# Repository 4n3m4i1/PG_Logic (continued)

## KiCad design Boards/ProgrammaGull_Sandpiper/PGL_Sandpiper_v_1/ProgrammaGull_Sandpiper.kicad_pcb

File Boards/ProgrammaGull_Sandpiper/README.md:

# ProgrammaGull Sandpiper
The Sandpiper is a complete educational development platform based on the Lattice UP5K.  
Designed for students in introductory FPGA labs and other interested parties.  
A plethora of user I/O options are integrated, allowing a complete system that can  
be used anywhere with minimal setup.

## Todo
v. Alpha
- Cleanup Layout
- Assess switching PSU
- Serialize Switch Inputs (Par -> Ser)
- Swap GPIO header to manufacturable part
- No ADC Version with 2x6 PMOD
- Add encoder, maybe bring back center DPAD button?
- Consolidate BOM (3x HCS595, discrete PNP and NPN driver for 7 seg)
  
## Errata
v. Alpha
- First board run has reversed UART TX/RX LED orientation (Fixed in KiCad files)
- First board run 7 segment common anode driver transistor bases leak through 74HCS596 input protection diode, all digits are always on. (Fixed in KiCad)

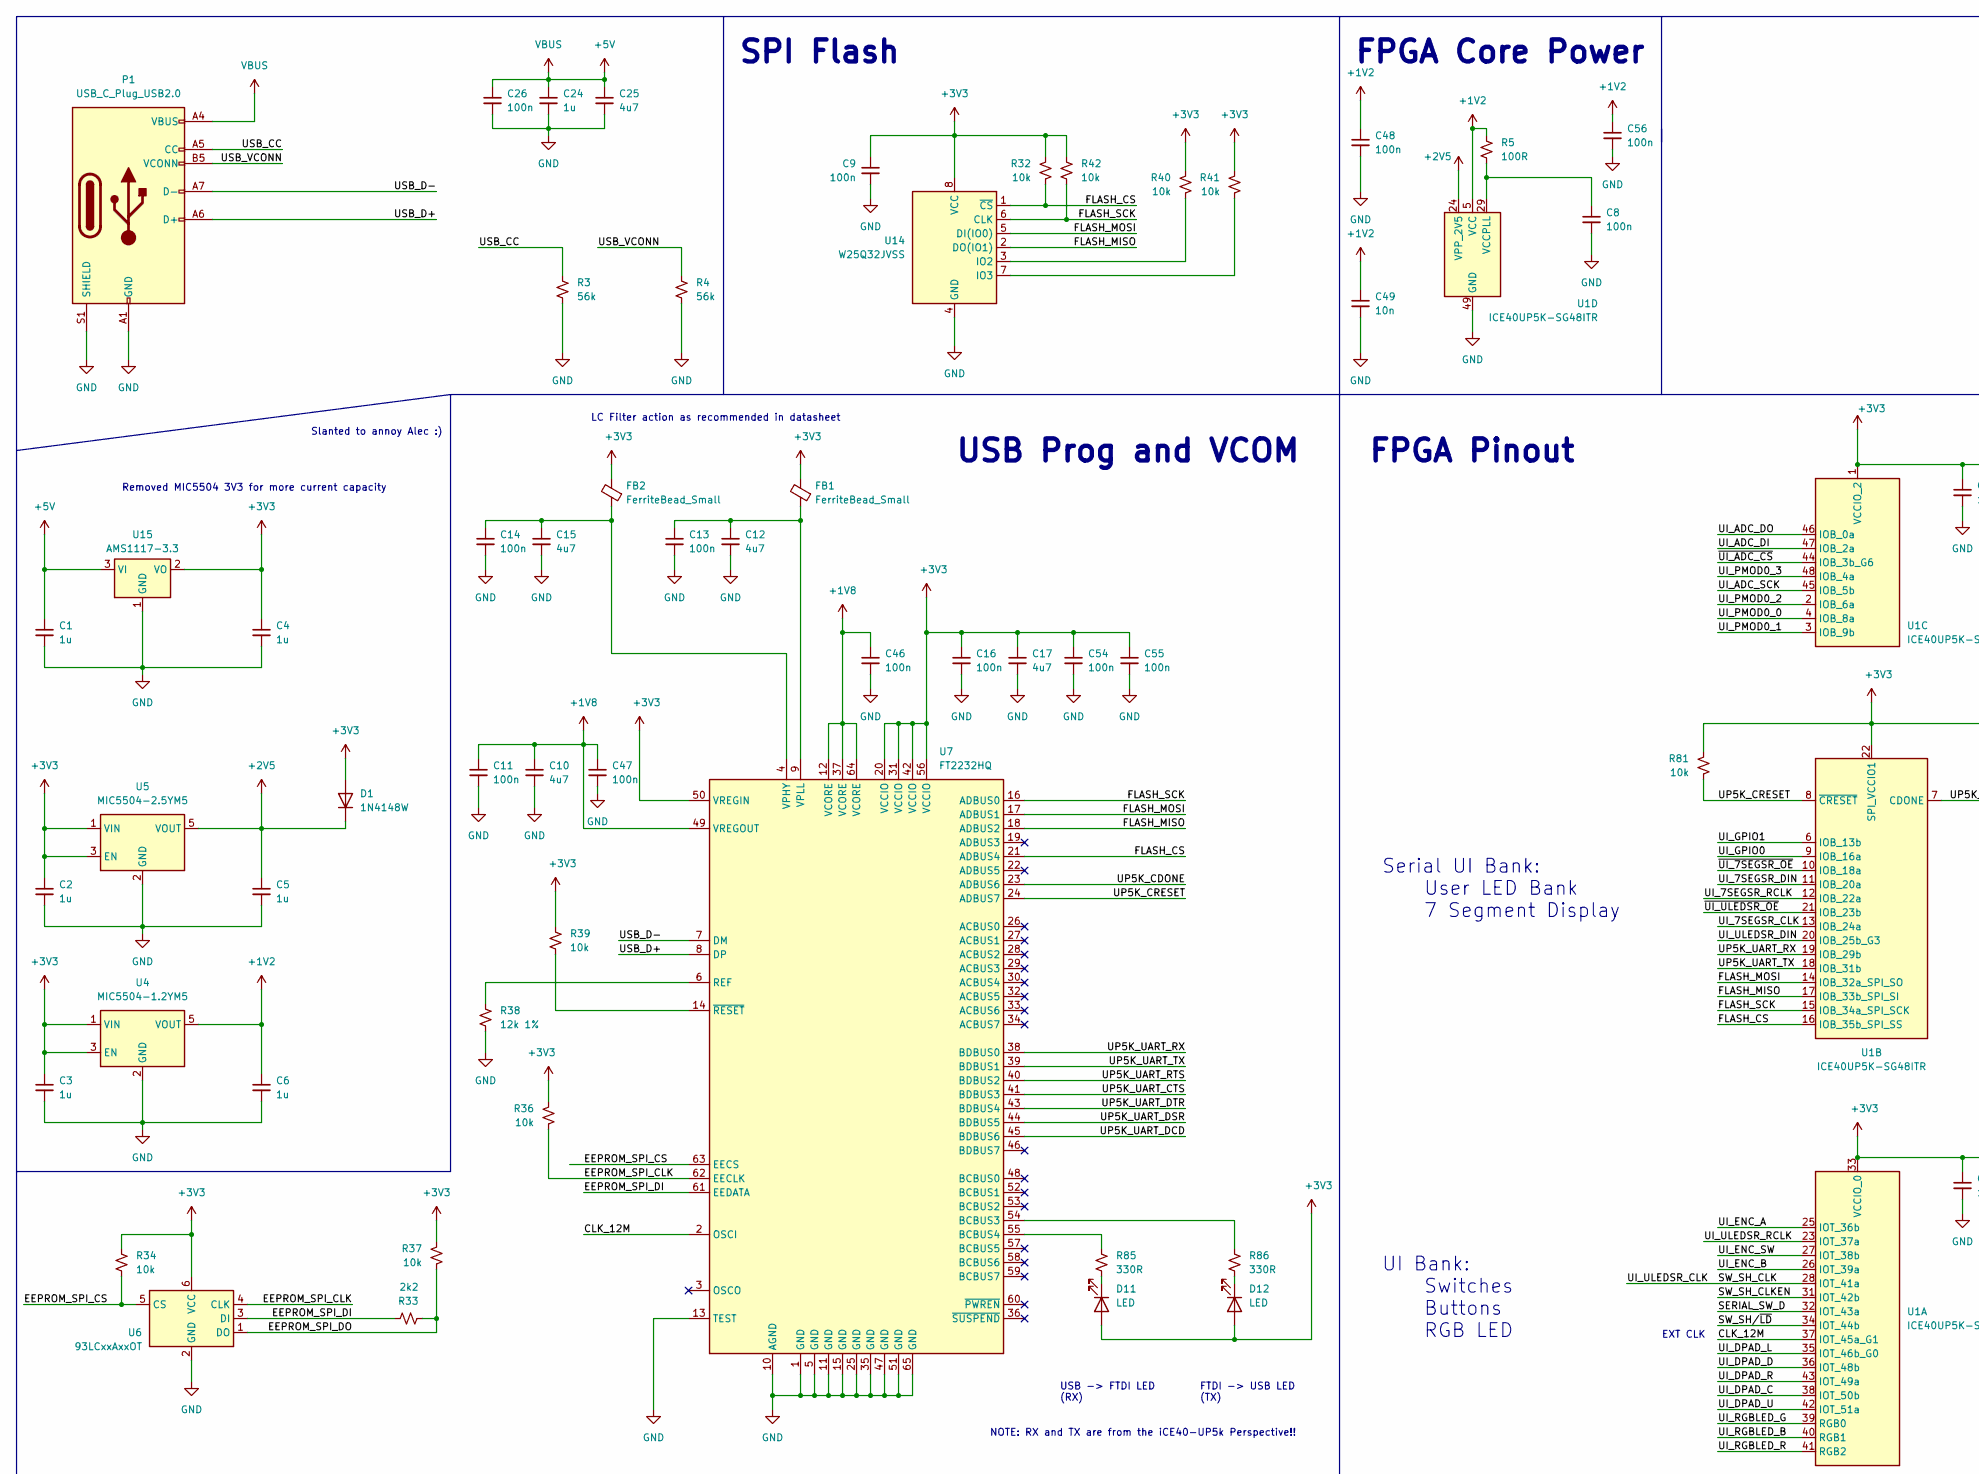
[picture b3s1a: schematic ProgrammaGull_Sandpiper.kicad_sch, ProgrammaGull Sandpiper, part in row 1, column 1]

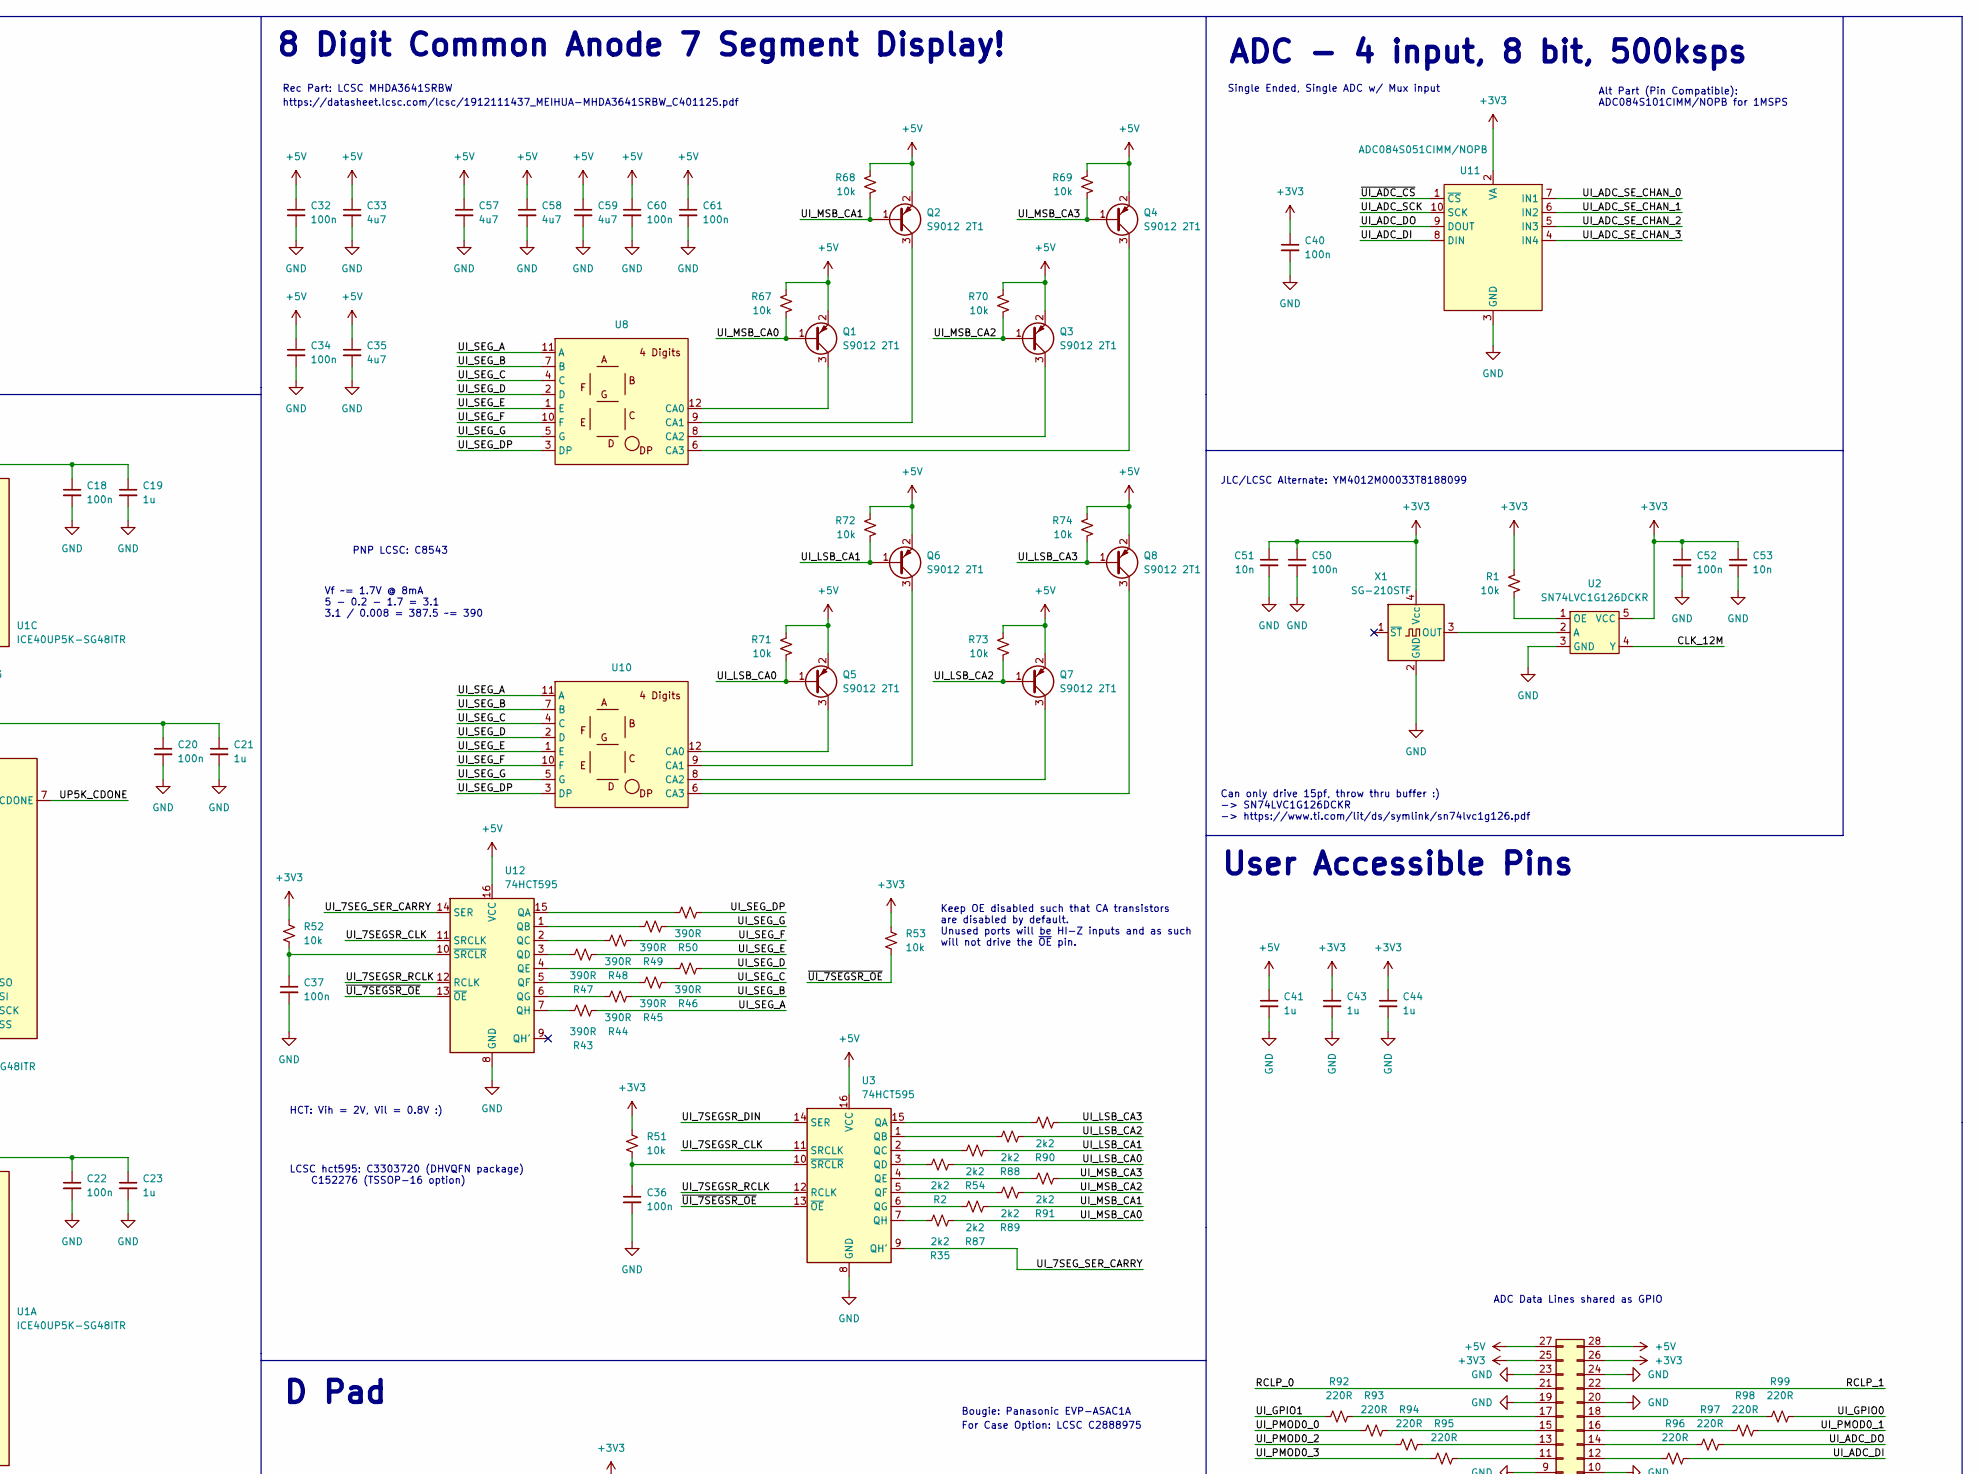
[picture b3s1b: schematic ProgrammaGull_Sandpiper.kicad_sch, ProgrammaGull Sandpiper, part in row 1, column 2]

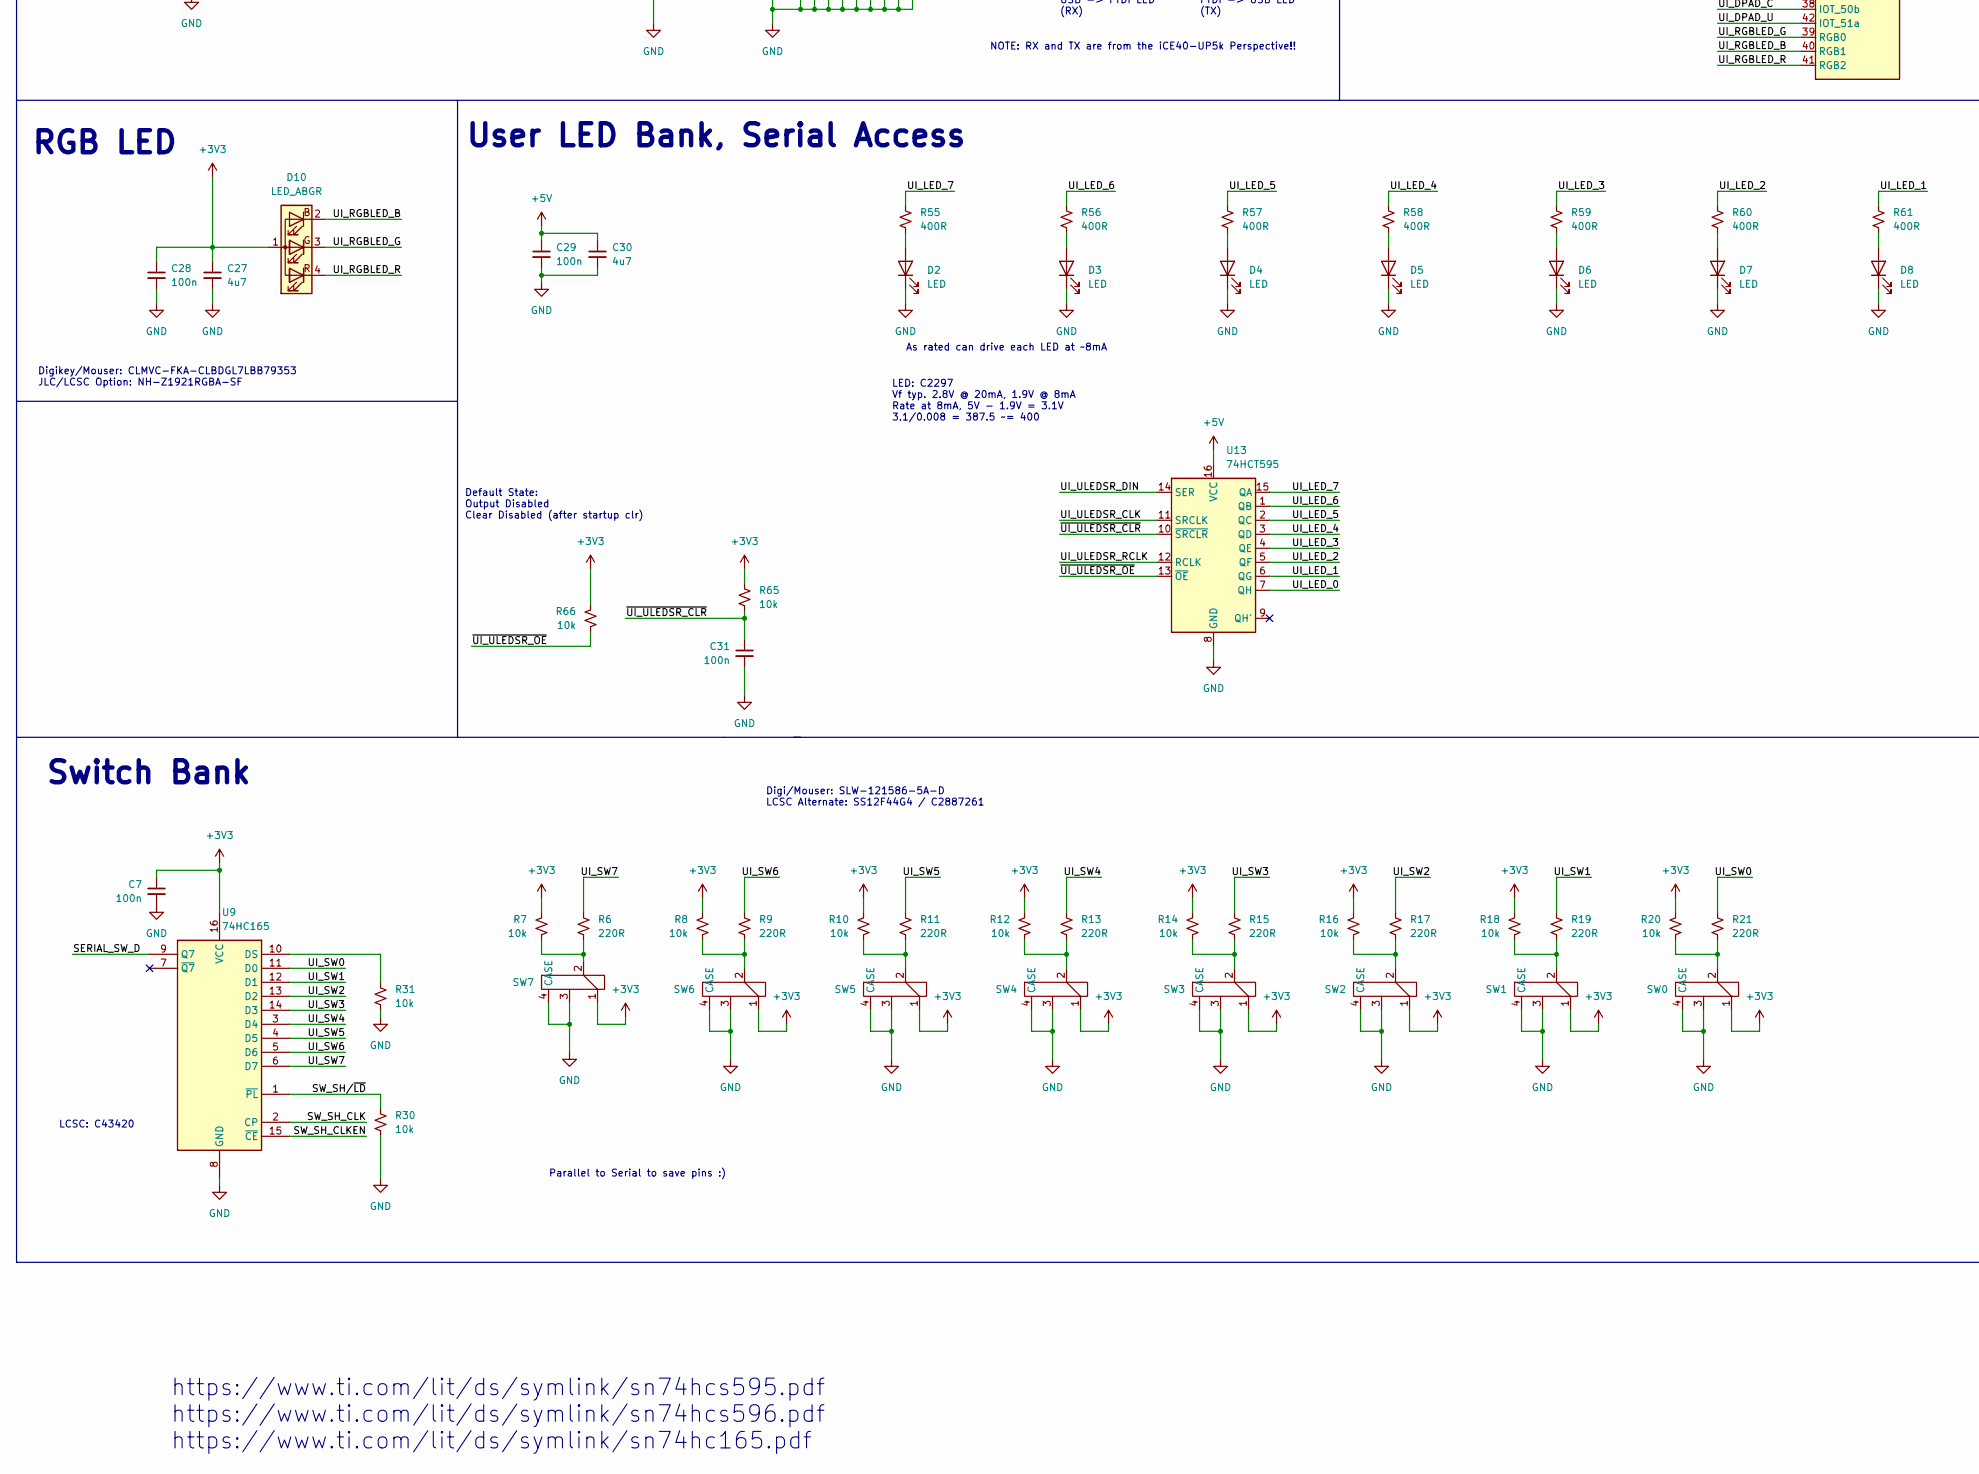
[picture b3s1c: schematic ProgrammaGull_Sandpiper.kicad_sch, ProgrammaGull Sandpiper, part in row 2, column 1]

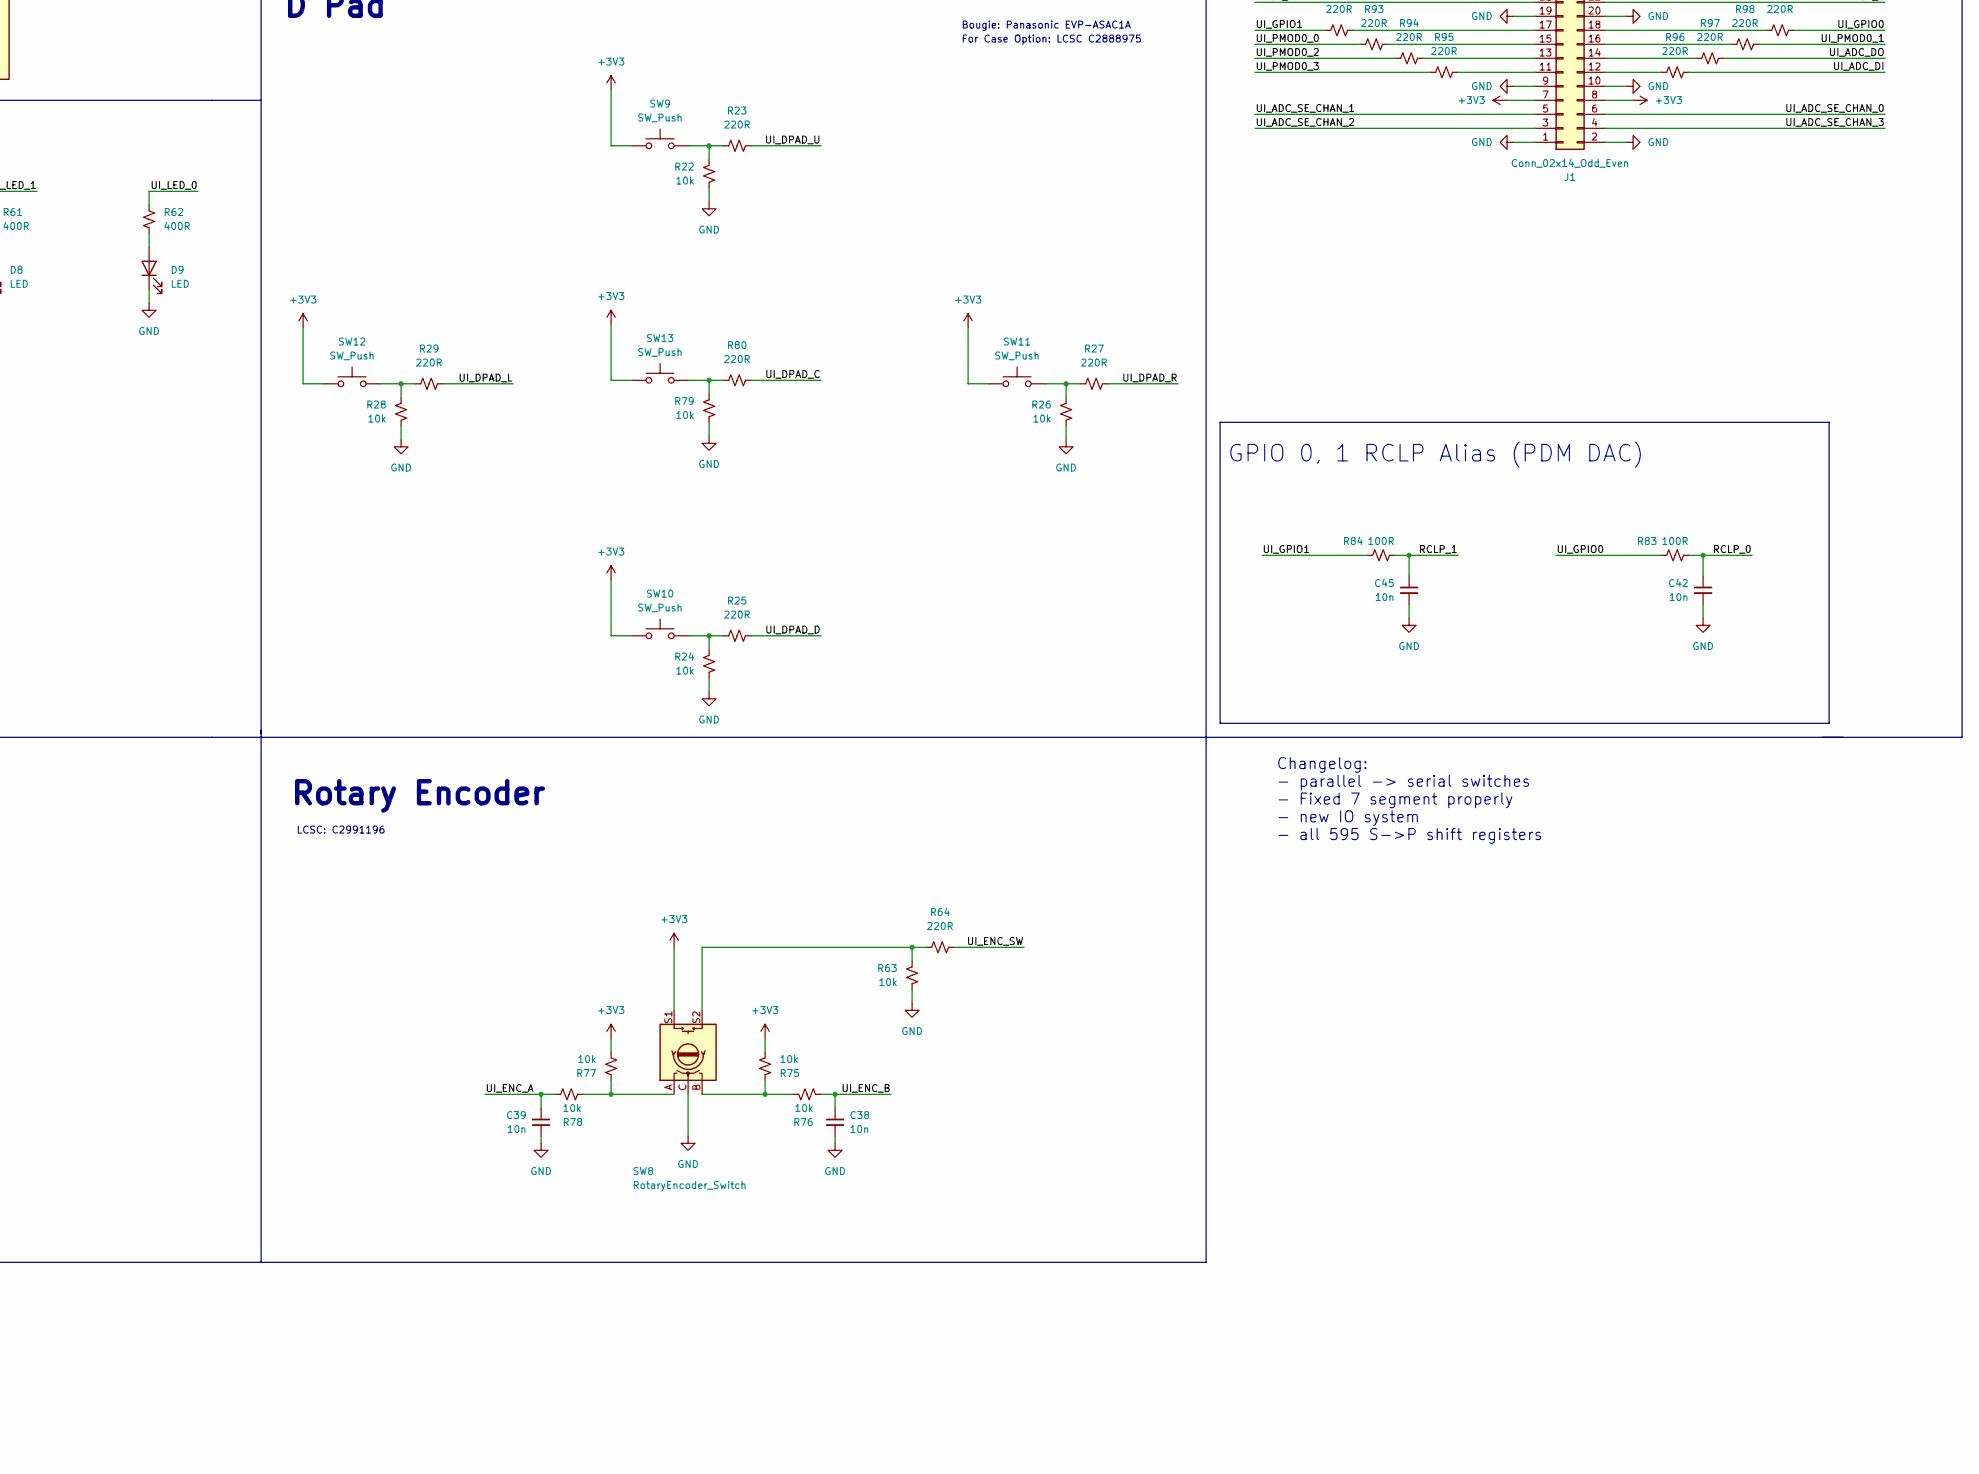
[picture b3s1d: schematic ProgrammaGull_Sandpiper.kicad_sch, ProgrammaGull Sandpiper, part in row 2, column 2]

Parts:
C1, C2, C3, C4, C5, C6, C19, C21, C23, C24, C41, C43, C44: 1u; C_0603_1608Metric
C7, C8, C9, C11, C13, C14, C16, C18, C20, C22, C26, C28, C29, C31, C32, C34, C36, C37, C40, C46, C47, C48, C50, C52, C54, C55, C56, C60, C61: 100n; C_0603_1608Metric
C10, C12, C15, C17, C25, C27, C30, C33, C35, C57, C58, C59: 4u7; C_0805_2012Metric
C38, C39, C42, C45, C49, C51, C53: 10n; C_0603_1608Metric
D1: 1N4148W; D_SOD-123
D2, D3, D4, D5, D6, D7, D8, D9, D11, D12: LED; LED_0805_2012Metric
D10: LED_ABGR; LED_Cree-PLCC4_2x2mm_CW
FB1, FB2: FerriteBead_Small; L_0603_1608Metric
J1: Conn_02x14_Odd_Even; PinSocket_2x14_P2.54mm_Horizontal
P1: USB_C_Plug_USB2.0; USB_C_Receptacle_GCT_USB4105-xx-A_16P_TopMnt_Horizontal
Q1, Q2, Q3, Q4, Q5, Q6, Q7, Q8: S9012 2T1; SOT-23
R1, R7, R8, R10, R12, R14, R16, R18, R20, R22, R24, R26, R28, R30, R31, R32, R34, R36, R37, R39, R40, R41, R42, R51, R52, R53, R63, R65, R66, R67, R68, R69, R70, R71, R72, R73, R74, R75, R76, R77, R78, R79, R81: 10k; R_0603_1608Metric
R2, R33, R35, R54, R87, R88, R89, R90, R91: 2k2; R_0603_1608Metric
R3, R4: 56k; R_0603_1608Metric
R5, R83, R84: 100R; R_0603_1608Metric
R6, R9, R11, R13, R15, R17, R19, R21: 220R; R_0603_1608Metric
R23, R25, R27, R29, R64, R80, R92, R93, R94, R95, R96, R97, R98, R99: 220R; R_0402_1005Metric
R38: 12k 1%; R_0603_1608Metric
R43, R44, R45, R46, R47, R48, R49, R50: 390R; R_0603_1608Metric
R55, R56, R57, R58, R59, R60, R61, R62: 400R; R_0603_1608Metric
R85, R86: 330R; R_0603_1608Metric
SW0, SW1, SW2, SW3, SW4, SW5, SW6, SW7: SLW-121586-5A-D
SW8: RotaryEncoder_Switch; RotaryEncoder_Alps_EC11E-Switch_Vertical_H20mm
SW9, SW10, SW11, SW12, SW13: SW_Push; TSC015A05518A
U1: ICE40UP5K-SG48ITR; QFN-48-1EP_7x7mm_P0.5mm_EP5.6x5.6mm
U2: SN74LVC1G126DCKR; SC70
U3, U12, U13: 74HCT595; DHVQFN-16-1EP_2.5x3.5mm_P0.5mm_EP1x2mm
U4: MIC5504-1.2YM5; SOT-23-5
U5: MIC5504-2.5YM5; SOT-23-5
U6: 93LCxxAxxOT; SOT-23-6
U7: FT2232HQ; QFN-64-1EP_9x9mm_P0.5mm_EP4.35x4.35mm
U8, U10: MHDA3641SRBW
U9: 74HC165; TSSOP-16_4.4x5mm_P0.65mm
U11: ADC084S051CIMM/NOPB; VSSOP-10_3x3mm_P0.5mm
U14: W25Q32JVSS; SOIC-8_5.23x5.23mm_P1.27mm
U15: AMS1117-3.3; SOT-223-3_TabPin2
X1: SG-210STF; Oscillator_SMD_SeikoEpson_SG210-4Pin_2.5x2.0mm

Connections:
+1V2: C6.1, C48.1, C49.1, C56.1, R5.2, U1.5 (VCC), U1.30 (VCC), U4.5 (VOUT)
+2V5: C5.1, D1.1 (K), U1.24 (VPP_2V5), U5.5 (VOUT)
+5V: C1.1, C24.1, C25.1, C26.1, C29.1, C30.1, C32.1, C33.1, C34.1, C35.1, C41.1, C57.1, C58.1, C59.1, C60.1, C61.1, J1.27, J1.28, P1.A4 (VBUS), P1.A9 (VBUS), P1.B4 (VBUS), P1.B9 (VBUS), Q1.2 (E), Q2.2 (E), Q3.2 (E), Q4.2 (E), Q5.2 (E), Q6.2 (E), Q7.2 (E), Q8.2 (E), R67.2, R68.2, R69.2, R70.2, R71.2, R72.2, R73.2, R74.2, U3.16 (VCC), U12.16 (VCC), U13.16 (VCC), U15.3 (VI)
/CLK_12M: U1.37 (IOT_45a_G1), U2.4 (Y), U7.2 (OSCI)
/EEPROM_SPI_CLK: R36.1, U6.4 (CLK), U7.62 (EECLK)
/EEPROM_SPI_CS: R34.1, U6.5 (CS), U7.63 (EECS)
/EEPROM_SPI_DI: R33.2, U6.3 (DI), U7.61 (EEDATA)
/EEPROM_SPI_DO: R33.1, R37.1, U6.1 (DO)
/FLASH_CS: R32.1, U1.16 (IOB_35b_SPI_SS), U7.21 (ADBUS4), U14.1 (~CS)
/FLASH_MISO: U1.17 (IOB_33b_SPI_SI), U7.18 (ADBUS2), U14.2 (DO(IO1))
/FLASH_MOSI: U1.14 (IOB_32a_SPI_SO), U7.17 (ADBUS1), U14.5 (DI(IO0))
/FLASH_SCK: R42.1, U1.15 (IOB_34a_SPI_SCK), U7.16 (ADBUS0), U14.6 (CLK)
/RCLP_0: C42.1, J1.21, R83.1
/RCLP_1: C45.1, J1.22, R84.1
/SERIAL_SW_D: U1.32 (IOT_43a), U9.9 (Q7)
/SW_SH_CLK: U1.28 (IOT_41a), U9.2 (CP), U13.11 (SRCLK)
/SW_SH_CLKEN: U1.31 (IOT_42b), U9.15 (~CE)
/SW_SH/~LD: R30.2, U1.34 (IOT_44b), U9.1 (~PL)
/UI_7SEGSR_CLK: U1.13 (IOB_24a), U3.11 (SRCLK), U12.11 (SRCLK)
/UI_7SEGSR_DIN: U1.11 (IOB_20a), U3.14 (SER)
/UI_7SEGSR_RCLK: U1.12 (IOB_22a), U3.12 (RCLK), U12.12 (RCLK)
/UI_7SEG_SER_CARRY: U3.9 (QH'), U12.14 (SER)
/UI_ADC_DI: R96.1, U1.47 (IOB_2a), U11.8 (DIN)
/UI_ADC_DO: R97.1, U1.46 (IOB_0a), U11.9 (DOUT)
/UI_ADC_SCK: U1.45 (IOB_5b), U11.10 (SCK)
/UI_ADC_SE_CHAN_0: J1.6, U11.7 (IN1)
/UI_ADC_SE_CHAN_1: J1.5, U11.6 (IN2)
/UI_ADC_SE_CHAN_2: J1.3, U11.5 (IN3)
/UI_ADC_SE_CHAN_3: J1.4, U11.4 (IN4)
/UI_DPAD_C: R80.1, U1.38 (IOT_50b)
/UI_DPAD_D: R25.1, U1.36 (IOT_48b)
/UI_DPAD_L: R29.1, U1.35 (IOT_46b_G0)
/UI_DPAD_R: R27.1, U1.43 (IOT_49a)
/UI_DPAD_U: R23.1, U1.42 (IOT_51a)
/UI_ENC_A: C39.1, R78.1, U1.25 (IOT_36b)
/UI_ENC_B: C38.1, R76.1, U1.26 (IOT_39a)
/UI_ENC_SW: R64.1, U1.27 (IOT_38b)
/UI_GPIO0: R83.2, R99.1, U1.9 (IOB_16a)
/UI_GPIO1: R84.2, R92.2, U1.6 (IOB_13b)
/UI_LED_0: R62.2, U13.7 (QH)
/UI_LED_1: R61.2, U13.6 (QG)
/UI_LED_2: R60.2, U13.5 (QF)
/UI_LED_3: R59.2, U13.4 (QE)
/UI_LED_4: R58.2, U13.3 (QD)
/UI_LED_5: R57.2, U13.2 (QC)
/UI_LED_6: R56.2, U13.1 (QB)
/UI_LED_7: R55.2, U13.15 (QA)
/UI_LSB_CA0: Q5.1 (B), R2.1, R71.1
/UI_LSB_CA1: Q6.1 (B), R54.1, R72.1
/UI_LSB_CA2: Q7.1 (B), R73.1, R88.1
/UI_LSB_CA3: Q8.1 (B), R74.1, R90.1
/UI_MSB_CA0: Q1.1 (B), R35.1, R67.1
/UI_MSB_CA1: Q2.1 (B), R68.1, R87.1
/UI_MSB_CA2: Q3.1 (B), R70.1, R89.1
/UI_MSB_CA3: Q4.1 (B), R69.1, R91.1
/UI_PMOD0_0: R93.2, U1.4 (IOB_8a)
/UI_PMOD0_1: R98.1, U1.3 (IOB_9b)
/UI_PMOD0_2: R94.2, U1.2 (IOB_6a)
/UI_PMOD0_3: R95.2, U1.48 (IOB_4a)
/UI_RGBLED_B: D10.2 (BK), U1.40 (RGB1)
/UI_RGBLED_G: D10.3 (GK), U1.39 (RGB0)
/UI_RGBLED_R: D10.4 (RK), U1.41 (RGB2)
/UI_SEG_A: R43.1, U8.11 (A), U10.11 (A)
/UI_SEG_B: R44.1, U8.7 (B), U10.7 (B)
/UI_SEG_C: R45.1, U8.4 (C), U10.4 (C)
/UI_SEG_D: R46.1, U8.2 (D), U10.2 (D)
/UI_SEG_DP: R50.1, U8.3 (DP), U10.3 (DP)
/UI_SEG_E: R47.1, U8.1 (E), U10.1 (E)
/UI_SEG_F: R48.1, U8.10 (F), U10.10 (F)
/UI_SEG_G: R49.1, U8.5 (G), U10.5 (G)
/UI_SW0: R21.2, U9.11 (D0)
/UI_SW1: R19.2, U9.12 (D1)
/UI_SW2: R17.2, U9.13 (D2)
/UI_SW3: R15.2, U9.14 (D3)
/UI_SW4: R13.2, U9.3 (D4)
/UI_SW5: R11.2, U9.4 (D5)
/UI_SW6: R9.2, U9.5 (D6)
/UI_SW7: R6.2, U9.6 (D7)
/UI_ULEDSR_DIN: U1.20 (IOB_25b_G3), U13.14 (SER)
/UI_ULEDSR_RCLK: U1.23 (IOT_37a), U13.12 (RCLK)
/UP5K_CDONE: U1.7 (CDONE), U7.23 (ADBUS6)
/UP5K_CRESET: R81.1, U1.8 (~CRESET), U7.24 (ADBUS7)
/UP5K_UART_CTS: U7.41 (BDBUS3)
/UP5K_UART_DCD: U7.45 (BDBUS6)
/UP5K_UART_DSR: U7.44 (BDBUS5)
/UP5K_UART_DTR: U7.43 (BDBUS4)
/UP5K_UART_RTS: U7.40 (BDBUS2)
/UP5K_UART_RX: U1.19 (IOB_29b), U7.38 (BDBUS0)
/UP5K_UART_TX: U1.18 (IOB_31b), U7.39 (BDBUS1)
/USB_CC: P1.A5 (CC), R3.2
/USB_D+: P1.A6 (D+), U7.8 (DP)
/USB_D-: P1.A7 (D-), U7.7 (DM)
/USB_VCONN: P1.B5 (VCONN), R4.2
/~UI_7SEGSR_OE: R53.1, U1.10 (IOB_18a), U3.13 (~OE), U12.13 (~OE)
/~UI_ADC_CS: U1.44 (IOB_3b_G6), U11.1 (~CS)
/~UI_ULEDSR_CLR: C31.1, R65.1, U13.10 (~SRCLR)
/~UI_ULEDSR_OE: R66.1, U1.21 (IOB_23b), U13.13 (~OE)
GND: C1.2, C2.2, C3.2, C4.2, C5.2, C6.2, C7.2, C8.2, C9.2, C10.2, C11.2, C12.2, C13.2, C14.2, C15.2, C16.2, C17.2, C18.2, C19.2, C20.2, C21.2, C22.2, C23.2, C24.2, C25.2, C26.2, C27.2, C28.2, C29.2, C30.2, C31.2, C32.2, C33.2, C34.2, C35.2, C36.2, C37.2, C38.2, C39.2, C40.2, C41.2, C42.2, C43.2, C44.2, C45.2, C46.2, C47.2, C48.2, C49.2, C50.2, C51.2, C52.2, C53.2, C54.2, C55.2, C56.2, C57.2, C58.2, C59.2, C60.2, C61.2, D2.1 (K), D3.1 (K), D4.1 (K), D5.1 (K), D6.1 (K), D7.1 (K), D8.1 (K), D9.1 (K), J1.1, J1.2, J1.9, J1.10, J1.19, J1.20, J1.23, J1.24, P1.A1 (GND), P1.A12 (GND), P1.B1 (GND), P1.B12 (GND), P1.S1 (SHIELD), R3.1, R4.1, R22.1, R24.1, R26.1, R28.1, R30.1, R31.1, R38.1, R63.1, R79.1, SW0.3, SW0.4 (CASE), SW1.3, SW1.4 (CASE), SW2.3, SW2.4 (CASE), SW3.3, SW3.4 (CASE), SW4.3, SW4.4 (CASE), SW5.3, SW5.4 (CASE), SW6.3, SW6.4 (CASE), SW7.3, SW7.4 (CASE), SW8.C, U1.49 (GND), U2.3 (GND), U3.8 (GND), U4.2 (GND), U5.2 (GND), U6.2 (GND), U7.1 (GND), U7.5 (GND), U7.10 (AGND), U7.11 (GND), U7.13 (TEST), U7.15 (GND), U7.25 (GND), U7.35 (GND), U7.47 (GND), U7.51 (GND), U7.65 (GND), U9.8 (GND), U11.3 (GND), U12.8 (GND), U13.8 (GND), U14.4 (GND), U15.1 (GND), X1.2 (GND); also elsewhere on the board
unnamed: D2.2 (A), R55.1
unnamed: D3.2 (A), R56.1
unnamed: D4.2 (A), R57.1
unnamed: D5.2 (A), R58.1
unnamed: D6.2 (A), R59.1
unnamed: D7.2 (A), R60.1
unnamed: D8.2 (A), R61.1
unnamed: D9.2 (A), R62.1
unnamed: D11.1 (K), R85.1
unnamed: D12.1 (K), R86.1
unnamed: J1.11, R95.1
unnamed: J1.12, R96.2
unnamed: J1.13, R94.1
unnamed: J1.14, R97.2
unnamed: J1.15, R93.1
unnamed: J1.16, R98.2
unnamed: J1.17, R92.1
unnamed: J1.18, R99.2
unnamed: Q1.3 (C), U8.12 (CA0)
unnamed: Q2.3 (C), U8.9 (CA1)
unnamed: Q3.3 (C), U8.8 (CA2)
unnamed: Q4.3 (C), U8.6 (CA3)
unnamed: Q5.3 (C), U10.12 (CA0)
unnamed: Q6.3 (C), U10.9 (CA1)
unnamed: Q7.3 (C), U10.8 (CA2)
unnamed: Q8.3 (C), U10.6 (CA3)
unnamed: R6.1, R7.1, SW7.2
unnamed: R8.1, R9.1, SW6.2
unnamed: R10.1, R11.1, SW5.2
unnamed: R12.1, R13.1, SW4.2
unnamed: R14.1, R15.1, SW3.2
unnamed: R16.1, R17.1, SW2.2
unnamed: R18.1, R19.1, SW1.2
unnamed: R20.1, R21.1, SW0.2
unnamed: R22.2, R23.2, SW9.2
unnamed: R24.2, R25.2, SW10.2
unnamed: R26.2, R27.2, SW11.2
unnamed: R28.2, R29.2, SW12.2
unnamed: R63.2, R64.2, SW8.S2
unnamed: R75.2, R76.2, SW8.B
unnamed: R77.2, R78.2, SW8.A
unnamed: R79.2, R80.2, SW13.2
unnamed: C8.1, R5.1, U1.29 (VCCPLL)
unnamed: U2.2 (A), X1.3 (OUT)
unnamed: R1.1, U2.1 (OE)
unnamed: R90.2, U3.15 (QA)
unnamed: R88.2, U3.1 (QB)
unnamed: R54.2, U3.2 (QC)
unnamed: R2.2, U3.3 (QD)
unnamed: R91.2, U3.4 (QE)
unnamed: R89.2, U3.5 (QF)
unnamed: R87.2, U3.6 (QG)
unnamed: R35.2, U3.7 (QH)
unnamed: C36.1, R51.1, U3.10 (~SRCLR)
unnamed: R86.2, U7.54 (BCBUS3)
unnamed: R85.2, U7.55 (BCBUS4)
unnamed: R38.2, U7.6 (REF)
unnamed: C14.1, C15.1, FB2.1, U7.4 (VPHY)
unnamed: C12.1, C13.1, FB1.1, U7.9 (VPLL)
unnamed: R39.1, U7.14 (~RESET)
unnamed: R31.2, U9.10 (DS)
unnamed: R50.2, U12.15 (QA)
unnamed: R49.2, U12.1 (QB)
unnamed: R48.2, U12.2 (QC)
unnamed: R47.2, U12.3 (QD)
unnamed: R46.2, U12.4 (QE)
unnamed: R45.2, U12.5 (QF)
unnamed: R44.2, U12.6 (QG)
unnamed: R43.2, U12.7 (QH)
unnamed: C37.1, R52.1, U12.10 (~SRCLR)
unnamed: R40.1, U14.3 (IO2)
unnamed: R41.1, U14.7 (IO3)

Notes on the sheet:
LED: C2297 Vf typ. 2.8V @ 20mA, 1.9V @ 8mA Rate at 8mA, 5V - 1.9V = 3.1V 3.1/0.008 = 387.5 ~= 400
FTDI -> USB LED (TX)
SPI Flash
PNP LCSC: C8543
User Accessible Pins
Slanted to annoy Alec :)
Keep OE disabled such that CA transistors are disabled by default. Unused ports will be HI-Z inputs and as such will not drive the ~{OE} pin.
Serial UI Bank: User LED Bank 7 Segment Display
Changelog: - parallel -> serial switches - Fixed 7 segment properly - new IO system - all 595 S->P shift registers
For Case Option: LCSC C2888975
Digikey/Mouser: CLMVC-FKA-CLBDGL7LBB79353 JLC/LCSC Option: NH-Z1921RGBA-SF
ADC - 4 input, 8 bit, 500ksps
Alt Part (Pin Compatible): ADC084S101CIMM/NOPB for 1MSPS
Removed MIC5504 3V3 for more current capacity
LCSC: C2991196
LCSC hct595: C3303720 (DHVQFN package) C152276 (TSSOP-16 option)
FPGA Core Power
Rotary Encoder
RGB LED
LC Filter action as recommended in datasheet
Vf ~= 1.7V @ 8mA 5 - 0.2 - 1.7 = 3.1 3.1 / 0.008 = 387.5 ~= 390
https://datasheet.lcsc.com/lcsc/1912111437_MEIHUA-MHDA3641SRBW_C401125.pdf
As rated can drive each LED at ~8mA
HCT: Vih = 2V, Vil = 0.8V :)
Bougie: Panasonic EVP-ASAC1A
Digi/Mouser: SLW-121586-5A-D LCSC Alternate: SS12F44G4 / C2887261
NOTE: RX and TX are from the iCE40-UP5k Perspective!!
8 Digit Common Anode 7 Segment Display!
USB -> FTDI LED (RX)
FPGA Pinout
GPIO 0, 1 RCLP Alias (PDM DAC)
Parallel to Serial to save pins :)
User LED Bank, Serial Access
EXT CLK
UI Bank: Switches Buttons RGB LED
Can only drive 15pf, throw thru buffer :) -> SN74LVC1G126DCKR -> https://www.ti.com/lit/ds/symlink/sn74lvc1g126.pdf
Rec Part: LCSC MHDA3641SRBW
https://www.ti.com/lit/ds/symlink/sn74hcs595.pdf https://www.ti.com/lit/ds/symlink/sn74hcs596.pdf https://www.ti.com/lit/ds/symlink/sn74hc165.pdf
Switch Bank
USB Prog and VCOM

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
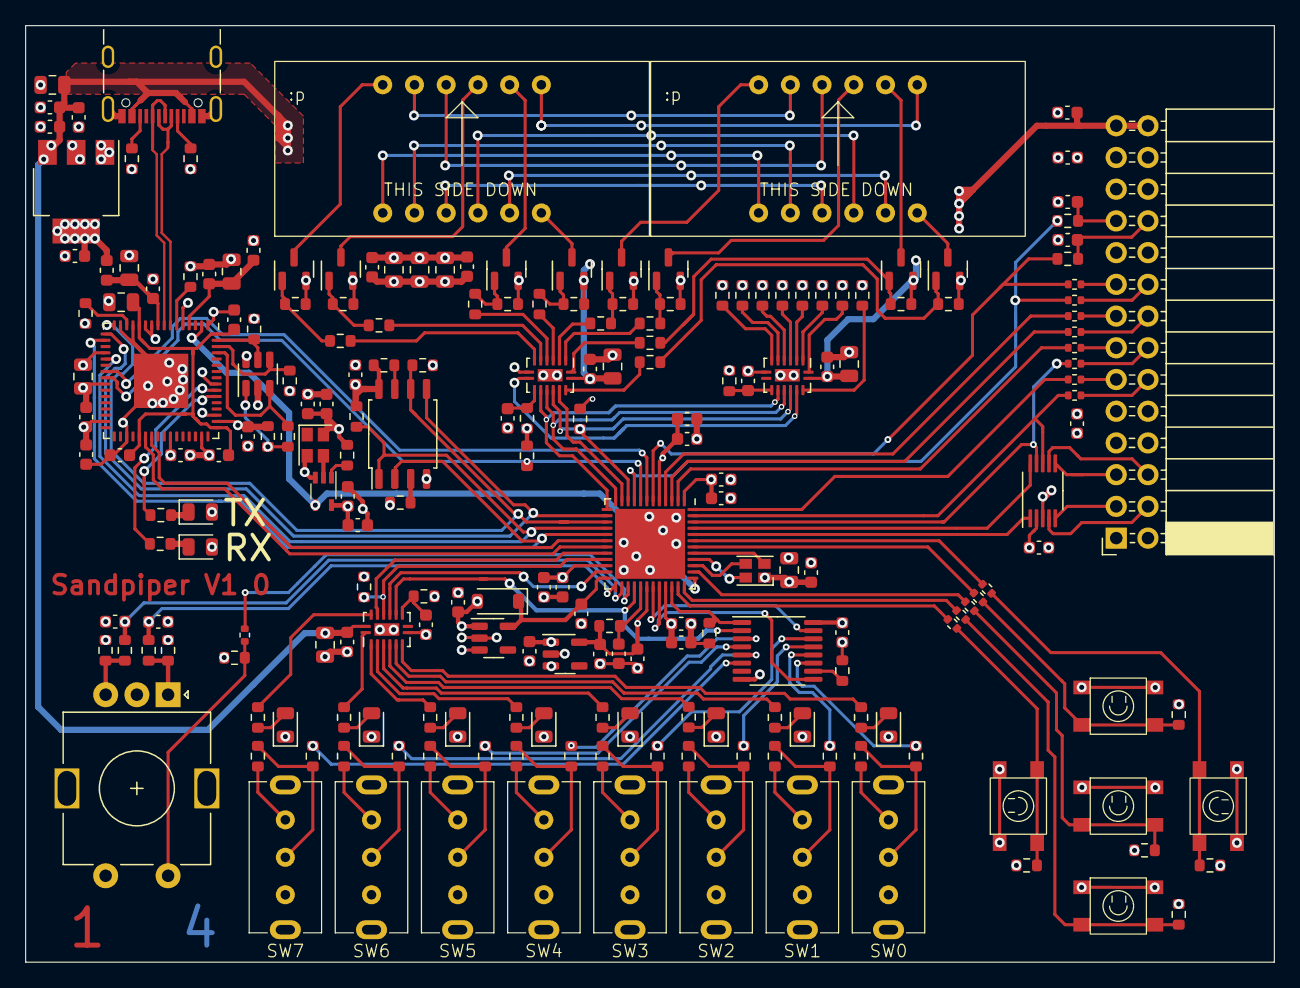
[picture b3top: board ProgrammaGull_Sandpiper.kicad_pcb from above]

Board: 4 copper layers, 100.0 x 75.0 mm, 214 parts (0 on the bottom side), 167 nets.

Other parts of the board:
C46#2: 100n; C_0603_1608Metric

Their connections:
GND: C46#2.2; also elsewhere on the board

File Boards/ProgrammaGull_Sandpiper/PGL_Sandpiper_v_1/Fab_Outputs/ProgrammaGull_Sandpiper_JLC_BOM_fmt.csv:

Designator,Qty,Value,Footprint,LCSC Part Number
"C1, C2, C3, C4, C5, C6, C19, C21, C23, C24, C41, C43, C44",13,1u,Capacitor_SMD:C_0603_1608Metric,C15849
"C7, C8, C9, C11, C13, C14, C16, C18, C20, C22, C26, C28, C29, C31, C32, C34, C36, C37, C40, C46, C47, C48, C50, C52, C54, C55, C56, C60, C61",29,100n,Capacitor_SMD:C_0603_1608Metric,C14663
"C10, C12, C15, C17, C25, C27, C30, C33, C35, C57, C58, C59",12,4u7,Capacitor_SMD:C_0805_2012Metric,C1779
"C38, C39, C42, C45, C49, C51, C53",7,10n,Capacitor_SMD:C_0603_1608Metric,C57112
D1,1,1N4148W,Diode_SMD:D_SOD-123,C81598
"D2, D3, D4, D5, D6, D7, D8, D9, D11, D12",10,LED,LED_SMD:LED_0805_2012Metric,C2297
D10,1,LED_ABGR,LED_SMD:LED_Cree-PLCC4_2x2mm_CW,C2874119
"FB1, FB2",2,FerriteBead_Small,Inductor_SMD:L_0603_1608Metric,C1002
J1,1,Conn_02x14_Odd_Even,Connector_PinSocket_2.54mm:PinSocket_2x14_P2.54mm_Horizontal,C2897434
P1,1,USB_C_Plug_USB2.0,Connector_USB:USB_C_Receptacle_GCT_USB4105-xx-A_16P_TopMnt_Horizontal,C963411
"Q1, Q2, Q3, Q4, Q5, Q6, Q7, Q8",8,S9012 2T1,Package_TO_SOT_SMD:SOT-23,C8543
"R1, R7, R8, R10, R12, R14, R16, R18, R20, R22, R24, R26, R28, R30, R31, R32, R34, R36, R37, R39, R40, R41, R42, R51, R52, R53, R63, R65, R66, R67, R68, R69, R70, R71, R72, R73, R74, R75, R76, R77, R78, R79, R81",43,10k,Resistor_SMD:R_0603_1608Metric,C25804
"R2, R33, R35, R54, R87, R88, R89, R90, R91",9,2k2,Resistor_SMD:R_0603_1608Metric,C4190
"R3, R4",2,56k,Resistor_SMD:R_0603_1608Metric,C23206
"R5, R83, R84",3,100R,Resistor_SMD:R_0603_1608Metric,C22775
"R6, R9, R11, R13, R15, R17, R19, R21",8,220R,Resistor_SMD:R_0603_1608Metric,C22962
"R23, R25, R27, R29, R64, R80, R92, R93, R94, R95, R96, R97, R98, R99",14,220R,Resistor_SMD:R_0402_1005Metric,C25091
R38,1,12k 1%,Resistor_SMD:R_0603_1608Metric,C22790
"R43, R44, R45, R46, R47, R48, R49, R50",8,390R,Resistor_SMD:R_0603_1608Metric,C23151
"R55, R56, R57, R58, R59, R60, R61, R62",8,400R,Resistor_SMD:R_0603_1608Metric,C23151
"R85, R86",2,330R,Resistor_SMD:R_0603_1608Metric,C23151
"SW0, SW1, SW2, SW3, SW4, SW5, SW6, SW7",8,~,ProgrammaGull_Logic:SLW-121586-5A-D,C2887261
SW8,1,RotaryEncoder_Switch,Rotary_Encoder:RotaryEncoder_Alps_EC11E-Switch_Vertical_H20mm,C2991196
"SW9, SW10, SW11, SW12, SW13",5,SW_Push,ProgrammaGull_Logic:TSC015A05518A,C2888975
U2,1,SN74LVC1G126DCKR,ProgrammaGull_Logic:SC70,C88039
"U3, U12, U13",3,74HCT595,Package_DFN_QFN:DHVQFN-16-1EP_2.5x3.5mm_P0.5mm_EP1x2mm,C3303720
U4,1,MIC5504-1.2YM5,Package_TO_SOT_SMD:SOT-23-5,C81462
U6,1,93LCxxAxxOT,Package_TO_SOT_SMD:SOT-23-6,C190271
U7,1,FT2232HQ,Package_DFN_QFN:QFN-64-1EP_9x9mm_P0.5mm_EP4.35x4.35mm,C193662
"U8, U10",2,~,ProgrammaGull_Logic:MHDA3641SRBW,C401125
U9,1,74HC165,Package_SO:TSSOP-16_4.4x5mm_P0.65mm,C43420
U14,1,W25Q32JVSS,Package_SO:SOIC-8_5.23x5.23mm_P1.27mm,C179173
U15,1,AMS1117-3.3,Package_TO_SOT_SMD:SOT-223-3_TabPin2,C6186
X1,1,SG-210STF,Oscillator:Oscillator_SMD_SeikoEpson_SG210-4Pin_2.5x2.0mm,C2831468
